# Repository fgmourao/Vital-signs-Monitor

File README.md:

<p align="right">

# Vital-signs Monitor v1.0
> **Under development**

Real-time, non-invasive physiological monitoring during experimental surgeries, stereotaxic procedures, and deep anaesthesia protocols in small rodents. ATmega2560 acquisition board controlled by a Python/PyQt5 application over USB, with simultaneous Wi-Fi browser dashboard via an on-board ESP8266.

---

## Overview

Four physiological parameters are acquired simultaneously:

- **Heart Rate** — MAX30102 optical sensor (IR channel), SparkFun `checkForBeat()` peak detector, rolling mean over N=6 beats; cleared to 0 after 5 s without an accepted beat (`HR_TIMEOUT_MS`)
- **SpO2** — MAX30102 Red + IR channels, Maxim `spo2_algorithm` (sliding window: retain 75, refill 25 per update); cleared to 0 after 10 s without a valid block (`SPO2_TIMEOUT_MS`)
- **Respiratory Rate** — respiratory sensor at A0 (piezo film or FSR406 pressure sensor), software Schmitt trigger with adaptive envelope calibration every 2 s
- **Core Temperature** — NTC 100 kΩ rectal thermistor (A1), Beta equation conversion

All parameters are streamed at ~100 Hz (measured ≈98 pkt/s, median timestamp spacing 10 ms) to the Python DAQ via USB-Serial and to a browser dashboard via WebSocket over Wi-Fi.

---

## Architecture

```
ATmega2560 (RobotDyn Mega+WiFi)
      │
      ├─ Serial0 (USB, 115200) ────────────────────────────────────────────────
      │        ↕ bidirectional JSON                                            │
      │   Py_VitalSigns_DAQ.py (PyQt5)                                        │
      │        outbound: {"hr":N,"sp":N,"rr":N,"pz":N,"t":N,"ir":N,"ts":N}   │
      │        inbound:  SOH + {"cmd":"set","key":"K","val":V}                 │
      │                  SOH + {"cmd":"get"}                                   │
      │                                                                        │
      ├─ Serial3 (pins 14/15, 115200) → ESP8266 (on-board) ──────────────────
      │        JSON 100 Hz stream → WebSocket → browser dashboard             │
      │                                                                        │
      ├─ I²C (pins 20/21)                                                     │
      │        ├─ MAX30102 optical sensor (address 0x57)                      │
      │        └─ SSD1306 OLED 128×32 (address 0x3C)                          │
      │                                                                        │
      ├─ A0 — Respiratory sensor (piezo film or FSR406 pressure sensor)       │
      ├─ A1 — NTC rectal thermistor                                            │
      │                                                                        │
      └─ Free-running ADC (~9.6 kHz) + TIMER1 CTC (100 Hz)                   │
               ISR decimation and Schmitt trigger for respiratory rate
```

---

## Signal Chain

### Heart Rate and SpO2

```
MAX30102 internal (400 Hz raw)
    └─ hardware averaging 4:1 → FIFO at 100 Hz
              │
              ├─ PATH 1 — Heart Rate
              │    checkForBeat(irRaw) at 100 Hz
              │    → _process_beat(): interval from sample index × measured sample period,
              │      physiological gate + outlier rejection
              │    → rolling mean N=6 → heartRate (BPM); 0 after HR_TIMEOUT_MS
              │
              └─ PATH 2 — SpO2
                   software decimation × g_DECIM_RATIO (default 1)
                   → irBuffer[100] + redBuffer[100]
                   → maxim_heart_rate_and_oxygen_saturation()
                   → sliding window (retain 75, refill 25) → spO2 (%); 0 after SPO2_TIMEOUT_MS
```

### Respiratory Rate

```
Respiratory sensor (A0)
    └─ ADC_vect free-running ~9.6 kHz (ISR)
              └─ TIMER1_COMPA_vect 100 Hz CTC (ISR)
                       └─ N=4 moving average
                                └─ software Schmitt trigger
                                         └─ adaptive envelope calibration every 2 s
                                                  └─ respRate (rpm)
```

### Respiratory Sensor Signal Conditioning (Python)

The raw ADC counts from the respiratory sensor are processed in Python before display and CSV recording:

1. **Unit conversion** — counts → mV (10-bit ADC, 5 V reference: 1 count ≈ 4.89 mV)
2. **DC baseline removal** — IIR low-pass filter (α = 0.005 @ 100 Hz, fc ≈ 0.08 Hz) tracks slow drift from animal weight and posture. Time constant ~200 s.
3. **Polarity correction** — controlled by `_INVERT_RESP` constant:
   - `True` (default): FSR406 and piezo where inspiration causes a voltage drop
   - `False`: piezo where inspiration already produces a positive peak
4. **Resp. Tare** — forces immediate convergence of the DC estimate when the animal is placed on the sensor

The same processing is applied in the browser dashboard JavaScript.

### Temporal Alignment

Both `ir` and `pz` are packed in the same JSON packet. The `"ts"` field carries `millis()` at packet serialisation time and is used by the Python DAQ as the common X-axis for both waveforms, eliminating USB transport jitter (~1–15 ms) from the recorded data.

---

## EEPROM Persistence

All mutable parameters (`g_*` variables) are saved to EEPROM on every change and restored on power-up. The first boot after a fresh firmware upload uses compile-time defaults; subsequent boots load the last saved values.

EEPROM layout (ATmega2560, 4 KB available):

| Addr | Variable | Type | Bytes |
|---|---|---|---|
| 0 | Magic byte (0xA6) | uint8_t | 1 |
| 1 | g_HR_MIN_BPM | float | 4 |
| 5 | g_HR_MAX_BPM | float | 4 |
| 9 | g_HR_OUTLIER_FRAC | float | 4 |
| 13 | g_SPO2_MIN_VALID | uint8_t | 1 |
| 14 | g_DECIM_RATIO | uint8_t | 1 |
| 15 | g_LED_BRIGHTNESS | uint8_t | 1 |
| 16 | g_SAMPLE_AVERAGE | uint8_t | 1 |
| 17 | g_ADC_RANGE | uint32_t | 4 |
| 21 | g_PULSE_WIDTH | uint16_t | 2 |
| 23 | g_CALIB_MIN_SWING | int | 4 |
| 27 | g_THRESH_INSP_FRAC | float | 4 |
| 31 | g_THRESH_EXP_FRAC | float | 4 |
| 35 | g_TEMP_MIN_C | float | 4 |
| 39 | g_TEMP_MAX_C | float | 4 |

---

## USB Protocol

Bidirectional JSON over Serial0 (115200 baud). Python prefixes every command with SOH (0x01) to halt the outbound 100 Hz stream before sending.

```
Outbound (100 Hz):
    {"hr":N,"sp":N,"rr":N,"pz":N,"t":N.N,"ir":N,"ts":N}

Inbound — set parameter:
    SOH + {"cmd":"set","key":"HR_MAX","val":500} + \n
    → {"ack":"HR_MAX","val":500.0000}
    → {"nak":"reason"}  (on failure)

Inbound — read all parameters:
    SOH + {"cmd":"get"} + \n
    → {"ack":"HR_MIN","val":40.0000}
       {"ack":"HR_MAX","val":800.0000}
       ... (one line per parameter)
```

### Configurable Parameters

| Key | Variable | Module | Description |
|---|---|---|---|
| `HR_MIN` | g_HR_MIN_BPM | MAX30102 | HR lower physiological gate (BPM) |
| `HR_MAX` | g_HR_MAX_BPM | MAX30102 | HR upper physiological gate (BPM) |
| `HR_OUTLIER` | g_HR_OUTLIER_FRAC | MAX30102 | Outlier rejection fraction (0.10–0.70) |
| `SPO2_MIN` | g_SPO2_MIN_VALID | MAX30102 | Minimum accepted SpO2 (%) |
| `DECIM_RATIO` | g_DECIM_RATIO | MAX30102 | SpO2 software decimation (1, 2, or 4) |
| `LED` | g_LED_BRIGHTNESS | MAX30102 | LED drive current (1–255) — reruns sensor setup |
| `ADC_RANGE` | g_ADC_RANGE | MAX30102 | ADC full-scale (2048/4096/8192/16384) — reruns setup |
| `SAMPLE_AVG` | g_SAMPLE_AVERAGE | MAX30102 | Hardware averaging per FIFO entry — reruns setup |
| `PULSE_WIDTH` | g_PULSE_WIDTH | MAX30102 | LED pulse width (69/118/215/411 µs) — reruns setup |
| `CALIB_SWING` | g_CALIB_MIN_SWING | monitor | Minimum respiratory sensor swing (mV) for valid calibration |
| `THRESH_INSP` | g_THRESH_INSP_FRAC | monitor | Inspiration threshold fraction (0.40–0.85) |
| `THRESH_EXP` | g_THRESH_EXP_FRAC | monitor | Expiration threshold fraction (0.20–0.70) |
| `TEMP_MIN` | g_TEMP_MIN_C | monitor | Temperature lower physiological gate (°C) |
| `TEMP_MAX` | g_TEMP_MAX_C | monitor | Temperature upper physiological gate (°C) |

---

## Wi-Fi Dashboard

The ESP8266 creates a Wi-Fi access point (`SSID: Vital_Signs_Web_Monitor`) and serves an HTML dashboard at `http://192.168.4.1`. A WebSocket server on port 81 forwards the 100 Hz JSON stream to connected browsers. The browser applies the same respiratory signal conditioning as the Python DAQ (mV conversion, DC removal, polarity correction).

Multi-client dispatch:
- **Primary client** (first to connect): receives every packet → 100 Hz
- **Secondary clients** (subsequent): receive 1 in 4 packets → 25 Hz

---

## Python Application

### Requirements

```
pip install pyserial PyQt5 pyqtgraph scipy numpy
```

Python 3.8 or later. Compatible with Spyder IDE.

### Features

- Real-time scrolling waveform display (IR-PPG and respiratory sensor)
- Numeric readouts: HR, SpO2, respiratory rate, core temperature
- Arduino timestamp (`"ts"`) used as the common X-axis — eliminates USB transport jitter from recorded data
- **Settings panel** — runtime adjustment of all sensor and algorithm parameters without recompilation; changes saved to EEPROM automatically; values auto-synced from Arduino on connect
- **Help panel** — parameter reference with species-specific suggested values and tooltips on every field
- **FFT viewer** — live power spectral density for both IR-PPG and respiratory channels (Welch method, configurable window and segment length)
- **Resp. Tare** — instant respiratory sensor baseline zeroing; cancels animal weight offset without waiting for IIR filter convergence
- **Event marker** — intra-session surgical event marking with visual timeline markers on both waveforms
- **CSV recording** split into two files:
  - `*_vitals.csv` — low-rate physiological values, wall-clock time axis
  - `*_raw.csv` — high-rate conditioned waveform samples, Arduino timestamp axis (`TS_Arduino_ms`)
- Pause / Resume without disconnecting

### CSV Output Format

**`*_vitals.csv`**

| Column | Description |
|---|---|
| Time_Seconds | Wall-clock elapsed time since REC start (s) |
| HeartRate_BPM | HR from MAX30102 ring buffer (BPM) |
| SpO2_% | SpO2 from Maxim algorithm (%) |
| RespRate_RPM | Respiratory rate from sensor detector (rpm) |
| Temperature_C | NTC rectal temperature (°C) |
| Event_Marker | "Event Start" on marked rows |

**`*_raw.csv`**

| Column | Description |
|---|---|
| Time_Seconds | Wall-clock elapsed time — for cross-reference only |
| TS_Arduino_ms | Arduino millis(), normalised to 0 at REC start — **use this as the time axis for signal analysis** |
| IR_Raw | Raw IR count from MAX30102 FIFO (counts, 18-bit) |
| Resp_mV | Respiratory sensor signal in mV — DC-removed and polarity-corrected; inspiration = positive peak. NOT the raw ADC value. |
| Event_Marker | 1 on event rows, 0 otherwise |

---

## Respiratory Sensor

The system is compatible with two sensor types connected to A0 via a voltage divider (R_fixed in series to VCC):

| Sensor type | R_fixed | Notes |
|---|---|---|
| FSR406 pressure sensor | 10 kΩ | Set `_INVERT_RESP = True`. Place under the animal. Target DC ~2500 mV with animal weight. |
| Piezo film sensor | Depends on interface circuit | Set `_INVERT_RESP` based on observed polarity. Inherently AC — Resp. Tare less critical. |

**Optimal operating point:** DC level ≈ 2500 mV (mid-range) with the animal positioned. If DC is below 1000 mV, reduce R_fixed. If above 4000 mV, increase R_fixed. Adjust Calib Min Swing (default 586 mV) downward for animals with shallow breathing.

---

## Species Reference Values

| Parameter | Human (bench) | Rat (anaest.) | Mouse (anaest.) |
|---|---|---|---|
| HR Min | 40 BPM | 200 BPM | 250 BPM |
| HR Max | 200 BPM | 500 BPM | 800 BPM |
| LED Brightness | 25 | 40–60 | 20–40 |
| ADC Range | 8192 | 4096 | 2048–4096 |
| Sample Average | 4 | 1–4 | 1–2 |
| Pulse Width | 215 µs | 215–411 µs | 215–411 µs |

Human bench values above (LED 25, ADC 8192) gave a stable HR and SpO2 record (AC peak-to-peak median ≈760 counts). Reference: LED 80 / ADC 16384 gave AC peak-to-peak ≈2240 counts, outside the `checkForBeat()` gate (see [T2]).

Target: IR AC peak-to-peak of **200–700 counts** per cardiac cycle (gate: >20 and <1000). Adjust LED until this holds; the AC amplitude scales with LED current. The IR DC level is secondary — avoid saturation (262,143) and verify in the waveform plot after positioning the sensor.

---

## Design Tradeoffs

**[T1] DECIM_RATIO = 1**
The Maxim `spo2_algorithm.cpp` FIR filters were designed for 25 Hz input (DECIM_RATIO = 4). With DECIM_RATIO = 1 the algorithm receives 100 Hz. Human bench tests show physiologically correct SpO2 (97–99%). Performance at rodent cardiac frequencies (300–600 BPM) is untested — if systematic SpO2 overestimation (e.g. constant 100%) is observed, increase DECIM_RATIO to 4 via Settings.

**[T2] checkForBeat() with hardware-averaged signal**
The SparkFun `checkForBeat()` detector was calibrated for unaveraged signals. With `sampleAverage = 4` the AC component is smoothed before detection. If HR detection fails on rodents, reduce `sampleAverage` to 1 via Settings to restore full AC amplitude at 400 Hz.

`checkForBeat()` accepts a beat only if the previous cycle's AC peak-to-peak is between 20 and 1000 counts; with a larger amplitude every beat is rejected (HR then stays at 0 after the timeout). Its 23-tap FIR low-pass (−3 dB ≈ 3 Hz) also strongly attenuates rodent cardiac frequencies (5–8 Hz: gain ≈0.36–0.04 relative to DC), so it is not expected to work reliably in rats and mice. The planned replacement is a band-pass (3.5–12 Hz) plus adaptive threshold detector (`alt_hr_detector.m`).

**[T3] ADC Range**
`adcRange = >8192` is required for human fingertip at LED = 25 to avoid saturation. For rodent thin tissue, try `adcRange = <4096` and verify IR raw in the waveform plot.

**[T4] IIR DC baseline convergence**
The respiratory signal DC filter has a time constant of ~200 s at 100 Hz. When the animal is first placed on the sensor, the display may appear shifted until the filter converges. Use **Resp. Tare** to force immediate convergence.

**[T5] SparkFun library internal buffer — STORAGE_SIZE**
The SparkFun MAX3010x library uses an internal ring buffer (`STORAGE_SIZE`) to hold FIFO data between `check()` calls. The default value of 4 samples causes silent data loss whenever `loop()` is delayed beyond ~40 ms (e.g. by the OLED display task), producing irregular sample spacing in `irBuffer[]` and `redBuffer[]`. This distorts the Maxim FIR filters and typically causes SpO2 to read 100% or HR to be erratic. The OLED is drawn page-wise (non-blocking), so `loop()` runs at ~10 ms, but the larger buffer is kept as a safeguard. This project set `STORAGE_SIZE = 64` by editing `MAX30105.h` at `~/Documents/Arduino/libraries/SparkFun_MAX3010x_Sensor_Library/src/MAX30105.h`

**[T6] SpO2 reference values**
The Maxim `spo2_algorithm` lookup table was calibrated for adult human fingertip measurements. In anaesthetised rodents, SpO2 values of 88–95% have been reported in the literature. If the monitor reads 99–100% during rodent anaesthesia, this may reflect algorithm miscalibration (next steps...)

---

## Hardware Requirements

| Component | Specification |
|---|---|
| Microcontroller | RobotDyn Mega+WiFi (ATmega2560 + ESP8266) |
| Optical sensor | MAX30102 breakout — I²C, address 0x57, 3.3 V |
| Display | SSD1306 OLED 128×32 — I²C, address 0x3C |
| Respiratory sensor | Piezo film or FSR406 → A0 (voltage divider with R_fixed to VCC) |
| Temperature probe | NTC 100 kΩ rectal thermistor → A1 (series 100 kΩ to VCC) |
| USB | ATmega2560 USB-Serial bridge (Arduino IDE upload port) |

---

## Files

| File | Description |
|---|---|
| `surgery_monitor.ino` | Main sketch — ISRs, task scheduler, OLED display, monitor_set_param() |
| `surgery_monitor_MAX30102.ino` | MAX30102 HR + SpO2, EEPROM persistence, max30102_set_param() |
| `Py_Vital-Signs.ino` | USB bidirectional stream — 100 Hz outbound + SOH command parser |
| `surgery_monitor_web_server.ino` | Serial3 → ESP8266 JSON bridge at 100 Hz |
| `ESP8266_VitalSigns_Server.ino` | ESP8266 firmware — Wi-Fi AP, HTTP dashboard, WebSocket multi-client |
| `MAX30102_Diagnostic_Tool.ino` | Standalone diagnostic sketch — IR waveform and SpO2 algorithm analysis |
| `Py_VitalSigns_DAQ.py` | Python DAQ application (PyQt5 + pyqtgraph) |
| `fft_vitalsigns.py` | Live PSD viewer — Welch method for HR and respiratory spectral analysis |
| `serial_rate_test.py` | Serial stream rate check (packets/s and timestamp spacing) |
| `emulate_firmware_hr.m` | MATLAB emulation of the firmware HR chain on `*_raw.csv` records |
| `alt_hr_detector.m` | MATLAB prototype of the alternative HR detector (band-pass + adaptive threshold) |

Arduino library dependencies (install via Arduino IDE Library Manager):
- **SparkFun MAX3010x Pulse and Proximity Sensor Library** ⚠️ requires manual modification (see [T5])
- **U8g2** (Oliver Kraus)
- **WebSockets** (Markus Sattler) — ESP8266 only

### Library Configuration

The SparkFun MAX3010x library requires one manual edit before compiling:

**File:** `~/Documents/Arduino/libraries/SparkFun_MAX3010x_Sensor_Library/src/MAX30105.h`

Locate and change:
```cpp
#define STORAGE_SIZE 4
```
to:
```cpp
#define STORAGE_SIZE 64  // required — default of 4 causes silent sample loss
```

This setting controls the size of the library's internal ring buffer. With the default of 4, any `loop()` delay beyond ~40 ms silently discards samples before they reach the HR and SpO2 algorithms, causing SpO2 to read 100% and HR to be erratic. See [T5] for the technical explanation.

---

## Known Limitations

- HR and SpO2 values are not validated against a calibrated reference instrument.
- SpO2 may read 100% consistently if `DECIM_RATIO = 1` (increase to 4 via Settings) or if the SparkFun library `STORAGE_SIZE` is not set to 64 (see [T5]).
- The plain-text diagnostic output (enabled with the `DEBUG_SERIAL` macro, default 0) is incompatible with the Python DAQ. Use only with the Arduino IDE Serial Monitor when the Python application is not connected.
- Opening the serial port resets the board (~3.5 s of boot text before the stream starts). Rate tests must discard this period.
- The HR detector (`checkForBeat()`) has not been validated in rodents (see [T2]).
- If the USB cable is disconnected during a recording session, the CSV files may be incomplete. Always stop recording before disconnecting.
- Primary Wi-Fi client assignment is first-connect order. If a secondary workstation connects before the primary, it will receive 25 Hz instead of 100 Hz.
- The Resp. Tare is session-only — it resets if the application is restarted or the connection is toggled.

---

## Author

**v1.0 (2026)**
Flavio Afonso Goncalves Mourao — [mourao.fg@gmail.com](mailto:mourao.fg@gmail.com)
*CNPq/MCTI/FNDCT Nº 21/2024 — Processo 446467/2024-3*
*Federal University of Minas Gerais, Brazil*

---

*Last update: October 2026*

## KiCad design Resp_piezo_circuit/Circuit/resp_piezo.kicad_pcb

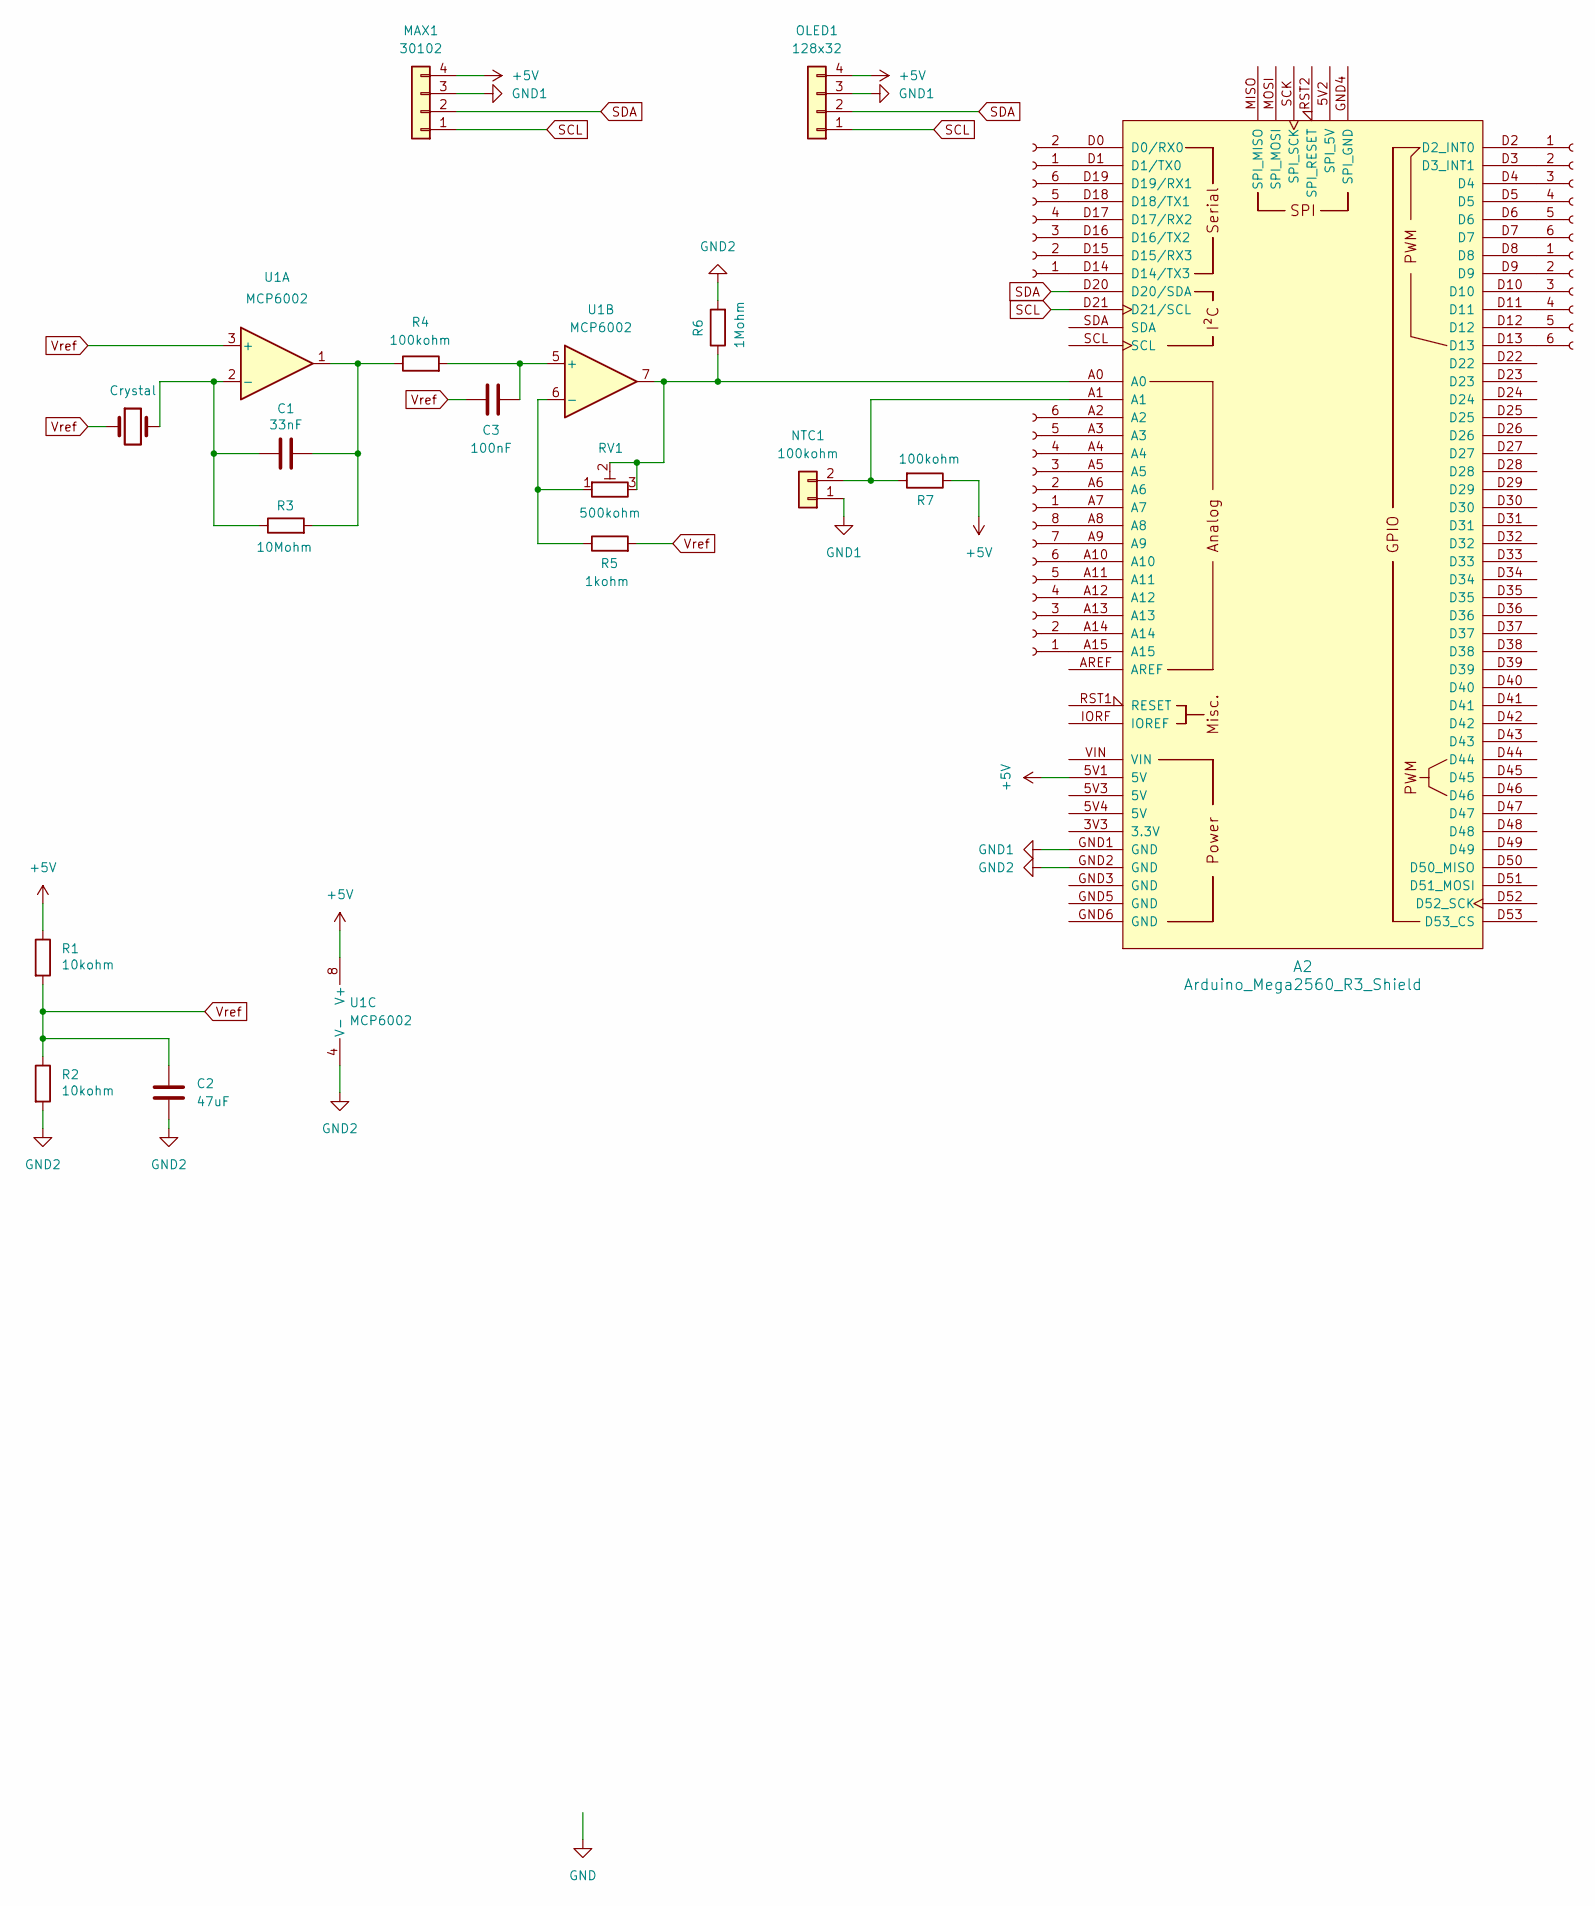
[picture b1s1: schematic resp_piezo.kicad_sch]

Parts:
A2: Arduino_Mega2560_R3_Shield
C1: 33nF; C_0805_2012Metric
C2: 47uF; C_0805_2012Metric
C3: 100nF; C_0805_2012Metric
J1, J3, J4: Conn_01x06_Socket; PinSocket_1x06_P2.54mm_Vertical
J2: Conn_01x06_Socket; PinHeader_1x06_P2.54mm_Vertical
J5: Conn_01x08_Socket; PinHeader_1x08_P2.00mm_Vertical
J6: Conn_01x02_Socket; PinSocket_1x02_P2.00mm_Vertical
MAX1: 30102; PinSocket_1x04_P2.54mm_Vertical
NTC1: 100kohm; PinSocket_1x02_P2.54mm_Vertical
OLED1: 128x32; PinSocket_1x04_P2.54mm_Vertical
R1, R2: 10kohm; R_0805_2012Metric
R3: 10Mohm; R_0805_2012Metric
R4, R7: 100kohm; R_0805_2012Metric
R5: 1kohm; R_0805_2012Metric
R6: 1Mohm; R_0805_2012Metric
RV1: 500kohm; PinHeader_1x03_P2.54mm_Vertical
U1: MCP6002; DIP787W46P254L927H533Q8
Y1: Crystal; PinHeader_1x02_P2.54mm_Vertical

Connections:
+5V: A2.5V1 (5V), MAX1.4, OLED1.4, R1.1, R7.1, U1.8 (V+)
GND1: A2.GND1 (GND), MAX1.3, NTC1.1, OLED1.3
GND2: A2.GND2 (GND), C2.2, R2.2, R6.2, U1.4 (V-), U1.9 (V-)
unnamed: A2.D0 (D0/RX0), J6.2
unnamed: A2.D1 (D1/TX0), J6.1
unnamed: A2.D2 (D2_INT0), J1.1
unnamed: A2.D3 (D3_INT1), J1.2
unnamed: A2.D14 (D14/TX3), J3.1
unnamed: A2.D15 (D15/RX3), J3.2
unnamed: A2.D16 (D16/TX2), J3.3
unnamed: A2.D17 (D17/RX2), J3.4
unnamed: A2.D18 (D18/TX1), J3.5
unnamed: A2.D19 (D19/RX1), J3.6
unnamed: A2.A0, R6.1, RV1.2, RV1.3, U1.7
unnamed: C1.2, R3.2, R4.1, U1.1
unnamed: A2.D4, J1.3
unnamed: A2.D5, J1.4
unnamed: A2.D6, J1.5
unnamed: A2.D7, J1.6
unnamed: A2.D8, J2.1
unnamed: A2.D9, J2.2
unnamed: A2.D10, J2.3
unnamed: A2.D11, J2.4
unnamed: A2.D12, J2.5
unnamed: A2.D13, J2.6
unnamed: A2.A7, J4.1
unnamed: A2.A6, J4.2
unnamed: A2.A5, J4.3
unnamed: A2.A4, J4.4
unnamed: A2.A3, J4.5
unnamed: A2.A2, J4.6
unnamed: A2.A15, J5.1
unnamed: A2.A14, J5.2
unnamed: A2.A13, J5.3
unnamed: A2.A12, J5.4
unnamed: A2.A11, J5.5
unnamed: A2.A10, J5.6
unnamed: A2.A9, J5.7
unnamed: A2.A8, J5.8
unnamed: A2.A1, NTC1.2, R7.2
unnamed: C1.1, R3.1, U1.2 (-), Y1.2
unnamed: C3.2, R4.2, U1.5 (+)
unnamed: R5.1, RV1.1, U1.6 (-)
SCL: A2.D21 (D21/SCL), MAX1.1, OLED1.1
SDA: A2.D20 (D20/SDA), MAX1.2, OLED1.2
Vref: C2.1, C3.1, R1.2, R2.1, R5.2, U1.3 (+), Y1.1

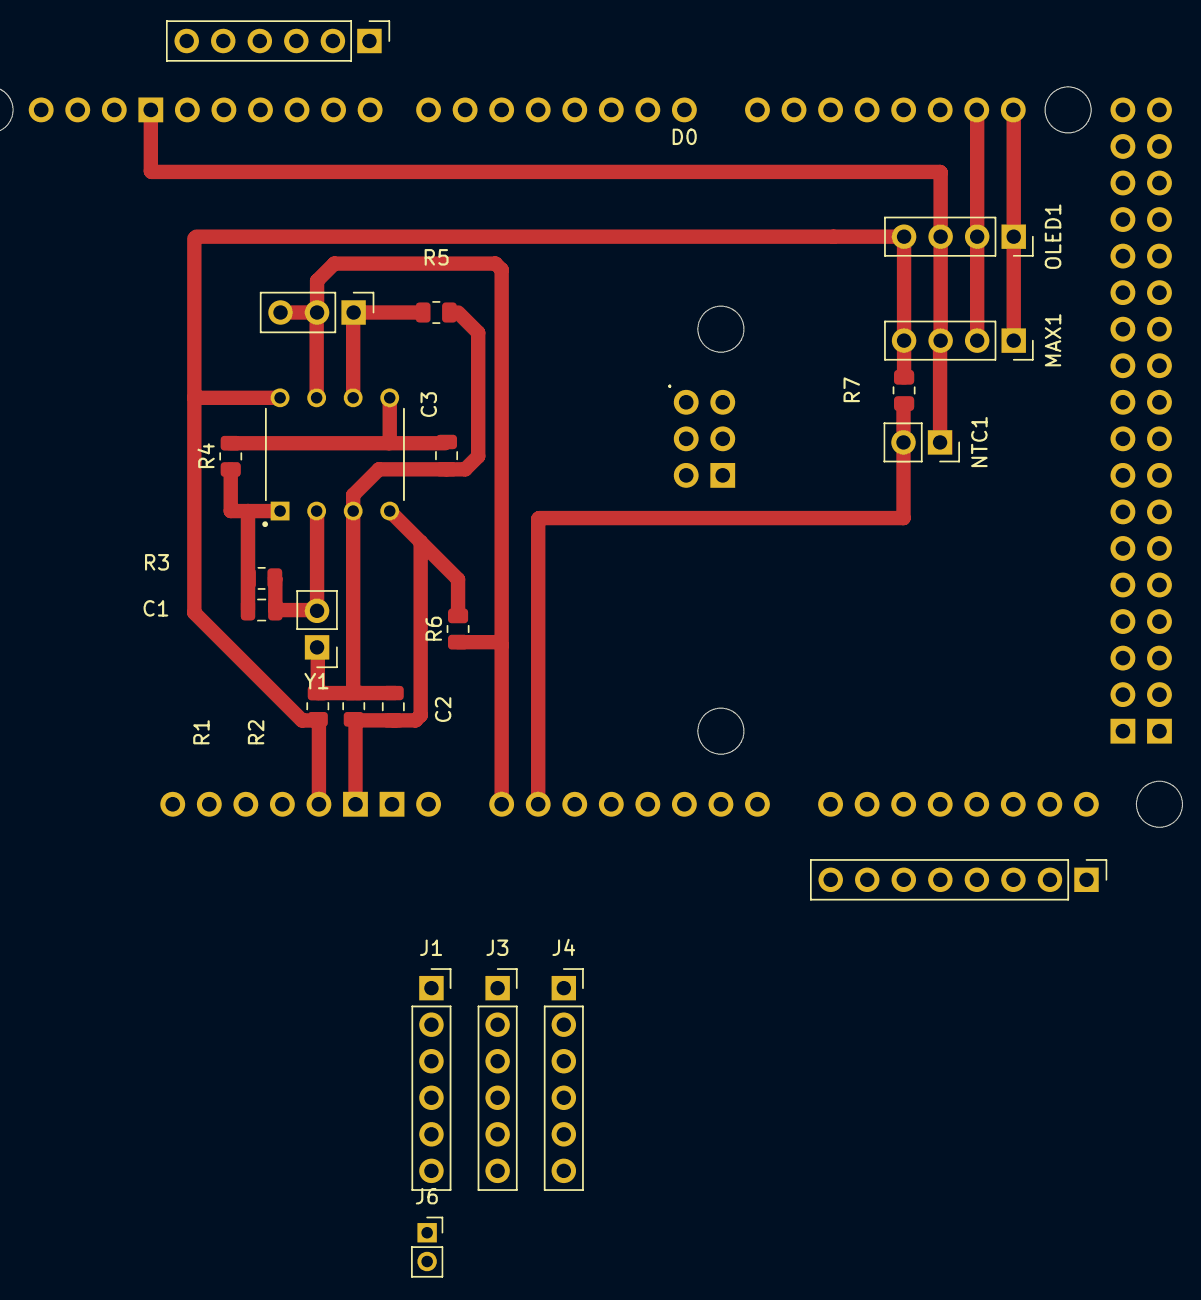
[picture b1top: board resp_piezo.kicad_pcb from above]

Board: 2 copper layers, 23 parts (0 on the bottom side), 46 nets.
